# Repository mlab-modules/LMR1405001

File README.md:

# LMR1405001 - High voltage high-power step-down converter

Used for power supply in 3D printers.

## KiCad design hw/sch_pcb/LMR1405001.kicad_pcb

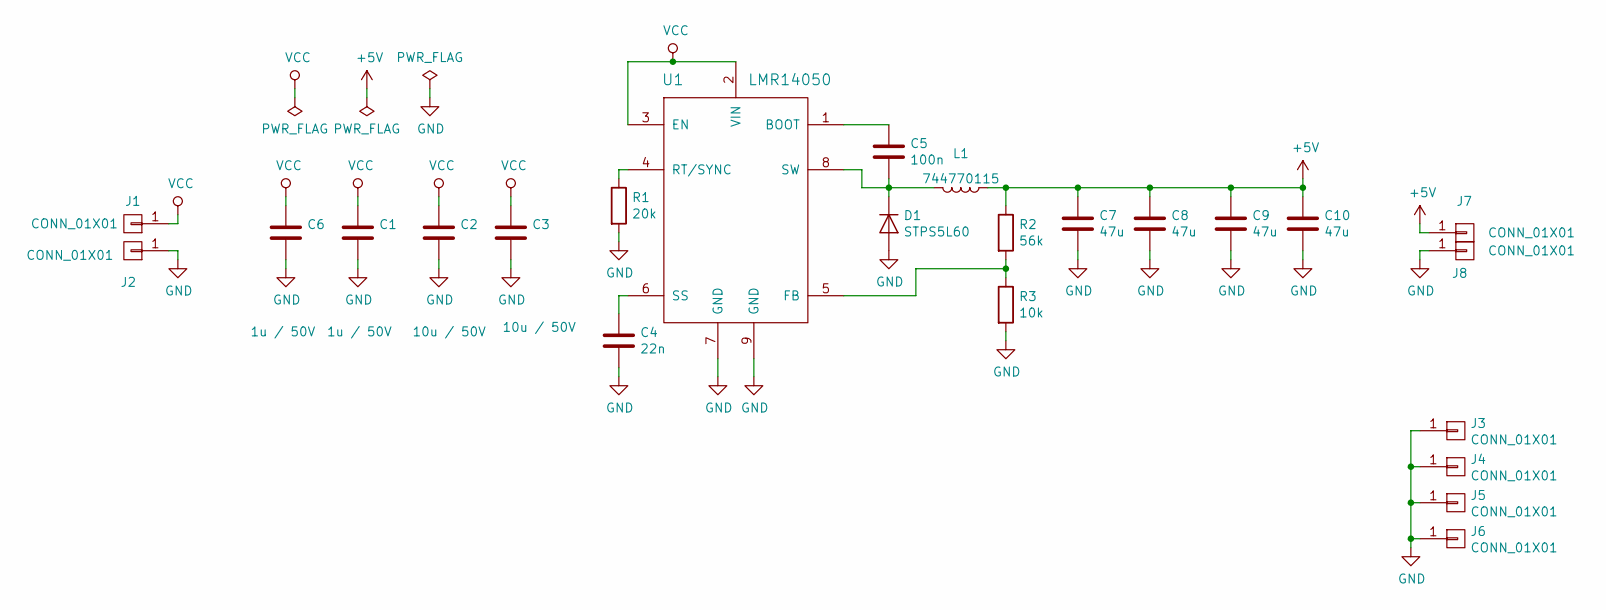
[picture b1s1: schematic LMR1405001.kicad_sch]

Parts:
C1, C6: 1u / 50V; C_1210
C2, C3: 10u / 50V; C_1210
C4: 22n; C_0603
C5: 100n; C_0603
C7, C8, C9, C10: 47u; C_1210
D1: STPS5L60; DO-214AB
J1, J2, J7, J8: CONN_01X01; WAGO256_2
J3, J4, J5, J6: CONN_01X01; MountingHole_3.2mm_M3_Pad
L1: 744770115; SELF-WE-PD-XXL
R1: 20k; C_0603
R2: 56k; C_0603
R3: 10k; C_0603
U1: LMR14050; HSOP-8

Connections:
+5V: C7.1, C8.1, C9.1, C10.1, J7.1, L1.2, R2.1
GND: C1.2, C2.2, C3.2, C4.2, C6.2, C7.2, C8.2, C9.2, C10.2, D1.2 (A), J2.1, J3.1, J4.1, J5.1, J6.1, J8.1, R1.2, R3.2, U1.7 (GND), U1.9 (GND)
unnamed: C5.2, D1.1 (K), L1.1, U1.8 (SW)
unnamed: C5.1, U1.1 (BOOT)
unnamed: R2.2, R3.1, U1.5 (FB)
unnamed: R1.1, U1.4 (RT/SYNC)
unnamed: C4.1, U1.6 (SS)
VCC: C1.1, C2.1, C3.1, C6.1, J1.1, U1.2 (VIN), U1.3 (EN)

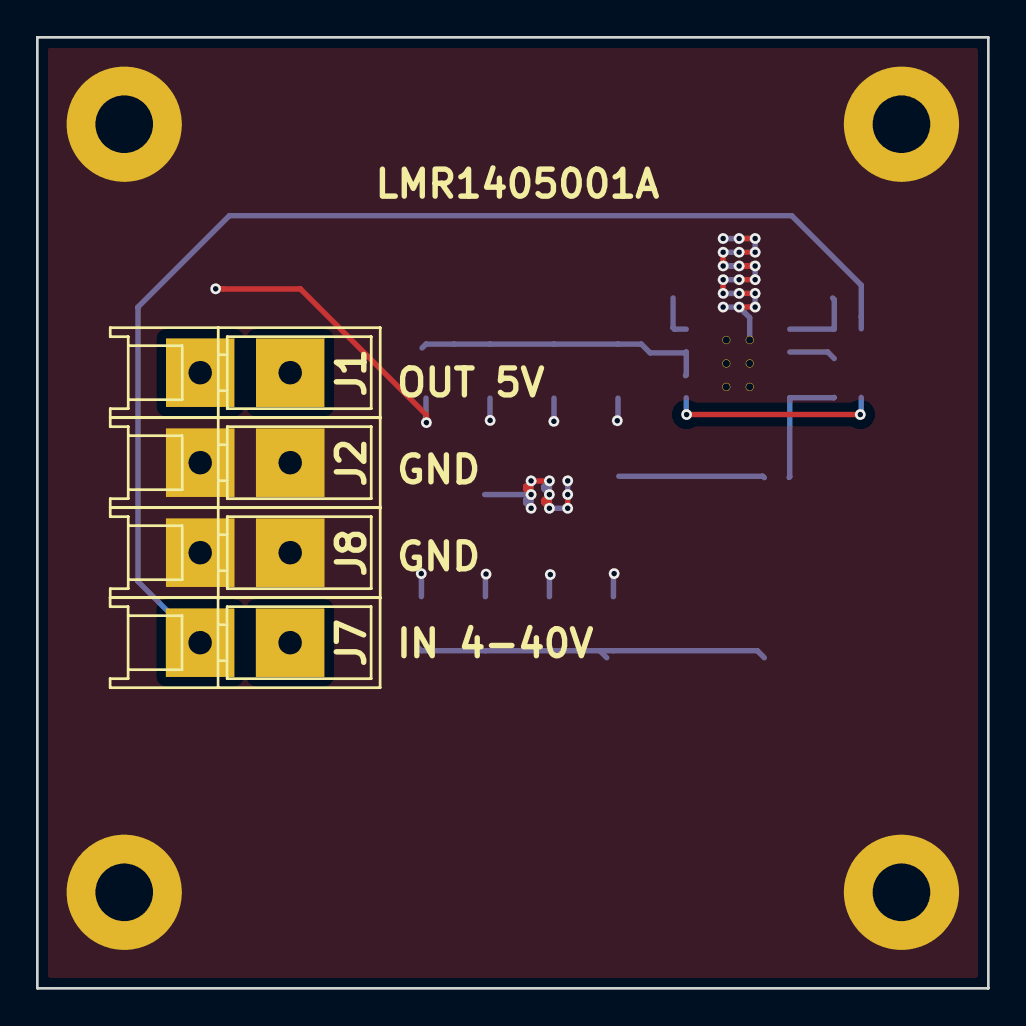
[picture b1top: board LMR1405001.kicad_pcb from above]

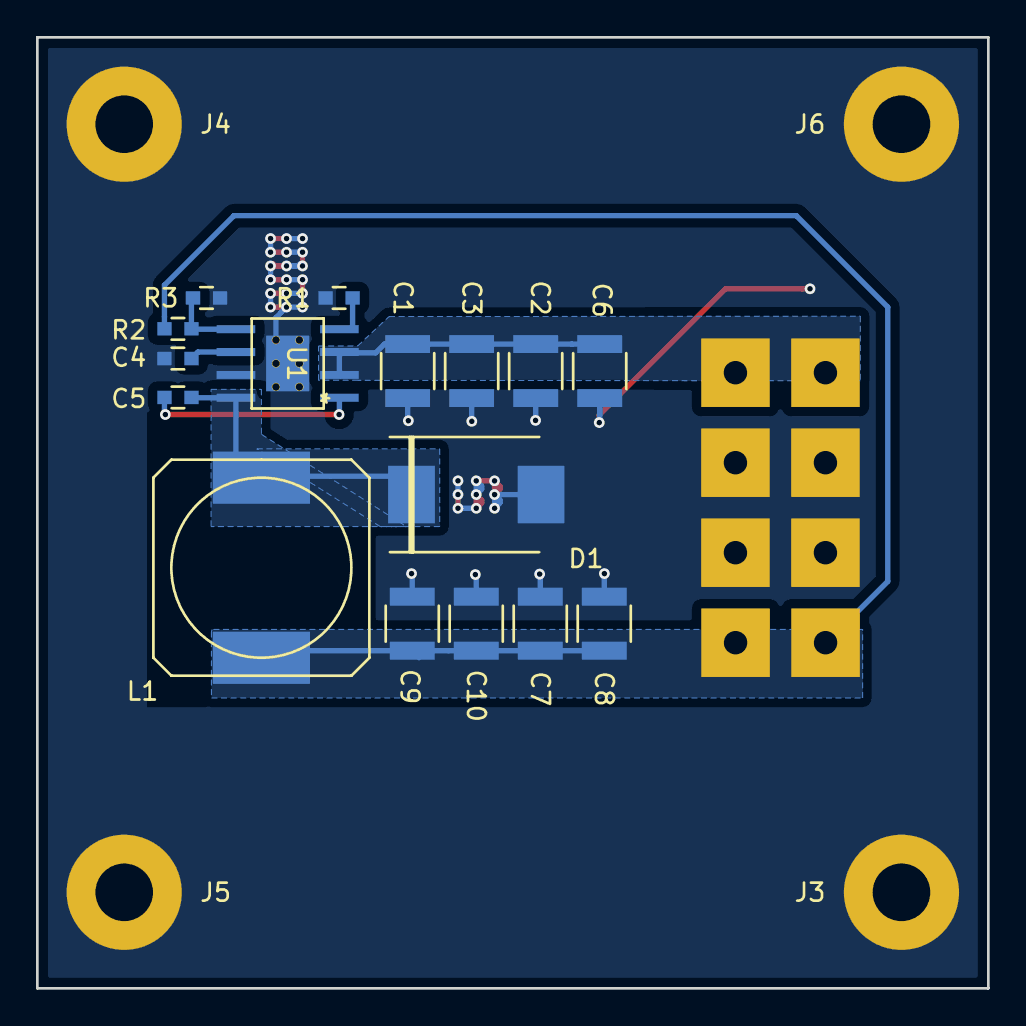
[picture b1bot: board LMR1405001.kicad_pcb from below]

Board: 2 copper layers, 52.8 x 52.8 mm, 24 parts (20 on the bottom side), 8 nets.

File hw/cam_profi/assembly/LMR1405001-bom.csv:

Component,Description,Part,References,Value,Footprint,Quantity Per PCB,Datasheet
1,,C,C4,22n,C_0603,1,
2,,C,C5,100n,C_0603,1,
3,,C,C7C8C9C10,47u,C_1210,4,
4,,C,C2C3,10u / 50V,C_1210,2,
5,,C,C1C6,1u / 50V,C_1210,2,
6,,D,D1,STPS5L60,DO-214AB,1,
7,,CONN_01X01,J1J2J7J8,CONN_01X01,WAGO256_2,4,
8,,L,L1,744770115,SELF-WE-PD-XXL,1,
9,,R,R3,10k,C_0603,1,
10,,R,R1,20k,C_0603,1,
11,,R,R2,56k,C_0603,1,
12,,LMR14050,U1,LMR14050,HSOP-8,1,

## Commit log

2018-01-28 LMR14050-PrvniVerze
2022-04-06 automated commit; add github actions
2023-05-28 Update metadata files
2023-06-15 Update workflow files
2023-09-16 Update status
2024-05-15 Change repository structure to conform MLAB standards.
2024-05-15 Change worksheet template. update module status.
2024-05-15 Update PCB from schematics.
2024-05-31 Update actions products
